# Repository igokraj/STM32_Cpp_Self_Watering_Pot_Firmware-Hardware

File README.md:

# Self Watering Pot

Projekt zakładał stworzenie automatycznej, samopodlewającej się doniczki na mikrokontrolerze STM32F446RE. Firmware jest napisany w C++. System pilnuje wilgotności gleby i sam włącza pompkę, kiedy gleba robi się za sucha. Da się też wymusić podlewanie ręcznie, a system ma kilka zabezpieczeń na wypadek, gdyby coś poszło nie tak (zaklinowana pompa, uszkodzony czujnik, zawieszony program, pusty pojemnik na wodę).

Do obsługi tego systemu spokojnie można by było użyć mikrokontrolera o mniejszej wydajności, liczbie pinów, pamięci..., jednak ze względu na to, że fizycznie do testowania posiadam jedynie NUCLEO-F446RE, to również na płytce PCB użyłem tego mikrokontrolera dla ujednolicenia projektu. Poniżej zamieszczam zdjęcia prototypu na płytce stykowej (jako zamiennik MOSFETa użyłem diody, symulując jego włączanie/wyłączanie, oraz jako czujnika wilgotności używam ręcznego potencjometru, a do czujnika poziomu wody po prostu kabla, który może być wpięty lub wypięty).

This project set out to build an automatic, self-watering plant pot based on the STM32F446RE microcontroller. The firmware is written in C++. The system keeps an eye on soil moisture and turns the pump on by itself once the soil gets too dry. Watering can also be forced manually, and the system has a few safeguards in case something goes wrong (a stuck pump, a broken sensor, a hung program, an empty water container).

This system would honestly run fine on a much smaller microcontroller which would have a less performance, fewer pins, less memory, but since the only board I physically had for testing was a NUCLEO-F446RE, I used the same chip on the PCB too, just to keep the project consistent. Below are photos of the prototype on a breadboard (I used an LED as a stand-in for the MOSFET, to simulate it switching on/off, a regular potentiometer as a stand-in for the moisture sensor, and for the water level sensor just a loose wire that can be plugged in or pulled out).

## Photos

**Breadboard prototype**

**Schematic**

**PCB layout and 3D render**

## How it works

The system has four states: **Waiting**, **Watering**, **EmptyContainer** (no water in the tank), and **Error**.

In the main loop, the program:

1. reads the water level sensor (float switch),
2. handles the Plus/Minus buttons (adjusts the target humidity by 10% per press, with auto-repeat while held) and the manual start button,
3. reads the soil moisture sensor and converts it to a percentage, checking along the way whether the reading looks like a broken/disconnected sensor,
4. decides the state based on that — with priority: pump fault > broken sensor > empty tank > humidity threshold,
5. drives the LEDs, pump, and buzzer, and shows everything on the OLED screen.

Watering kicks in once humidity drops noticeably (by 15 percentage points). If the pump runs continuously for more than 15 seconds, the system treats it as a fault, shuts the pump off for good, and requires a manual reset via the Start button — the buzzer beeps 3 times during this, repeating once a minute.

Holding the Manual Start button forces watering regardless of what the sensor reads.

## Peripherals / electronics

- **STM32F446RETx** — microcontroller
- **Soil moisture sensor** (capacitive) — ADC input
- **Water level sensor** (float switch) — a plain switch
- **3× buttons** — Manual Start, Plus, Minus
- **RGB LED** — indicates system state by color
- **Buzzer** — audible alarm on error
- **Water pump** driven by a MOSFET (IRLZ540N)
- **128×64 OLED display** (SSD1306) over I2C
- **AMS1117-3.3** — 3.3V voltage regulator
- Power connector (barrel jack) with a fuse and overvoltage protection
- SWD connector (ST-Link) for programming/debugging

## BOM (short version)

| Reference      | Component                                                             | Qty |
| --------------- | --------------------------------------------------------------------- | --- |
| U2              | STM32F446RETx                                                         | 1   |
| U1              | AMS1117-3.3 (3.3V regulator)                                          | 1   |
| Q1              | IRLZ540N (MOSFET, pump switch)                                        | 1   |
| RGB1            | RGB LED                                                                | 1   |
| LED1            | LED (status)                                                          | 1   |
| Buzzer1         | Buzzer                                                                 | 1   |
| SW1–SW3         | Buttons (Start/Plus/Minus)                                            | 3   |
| J1              | Power jack (barrel jack)                                               | 1   |
| J5, J6          | Screw terminals (pump, external power)                                | 2   |
| Hum Sensor1     | Moisture sensor connector                                              | 1   |
| OLED1           | OLED display connector                                                 | 1   |
| STLink1         | Programmer connector                                                   | 1   |
| F1              | Fuse                                                                    | 1   |
| D2              | TVS diode (overvoltage protection)                                     | 1   |
| D3, D4, D6–D11  | Schottky diodes                                                        | 8   |
| L1              | Ferrite bead (power filtering)                                         | 1   |
| R, C            | Resistors and capacitors (filtering, pull-up/down, debounce circuits) | ~30 |

The full list (with LCSC part numbers) is in `hardware/Self_Watering_POT/BOM.xlsx` and `All_BOM.xlsx`.

## Firmware

The code is written in **C++** (built on top of the C code generated by STM32CubeMX/HAL). The pot's state logic, debounced button handling, OLED display, and buzzer are written as separate classes/modules — the rest (ADC, timer, GPIO, watchdog) is the generated HAL layer.

## Repo structure

- `firmware/` — CMake project with the STM32 sources
- `hardware/` — KiCad schematic and PCB, production files (Gerbers), BOM
- `Images/` — project photos and renders

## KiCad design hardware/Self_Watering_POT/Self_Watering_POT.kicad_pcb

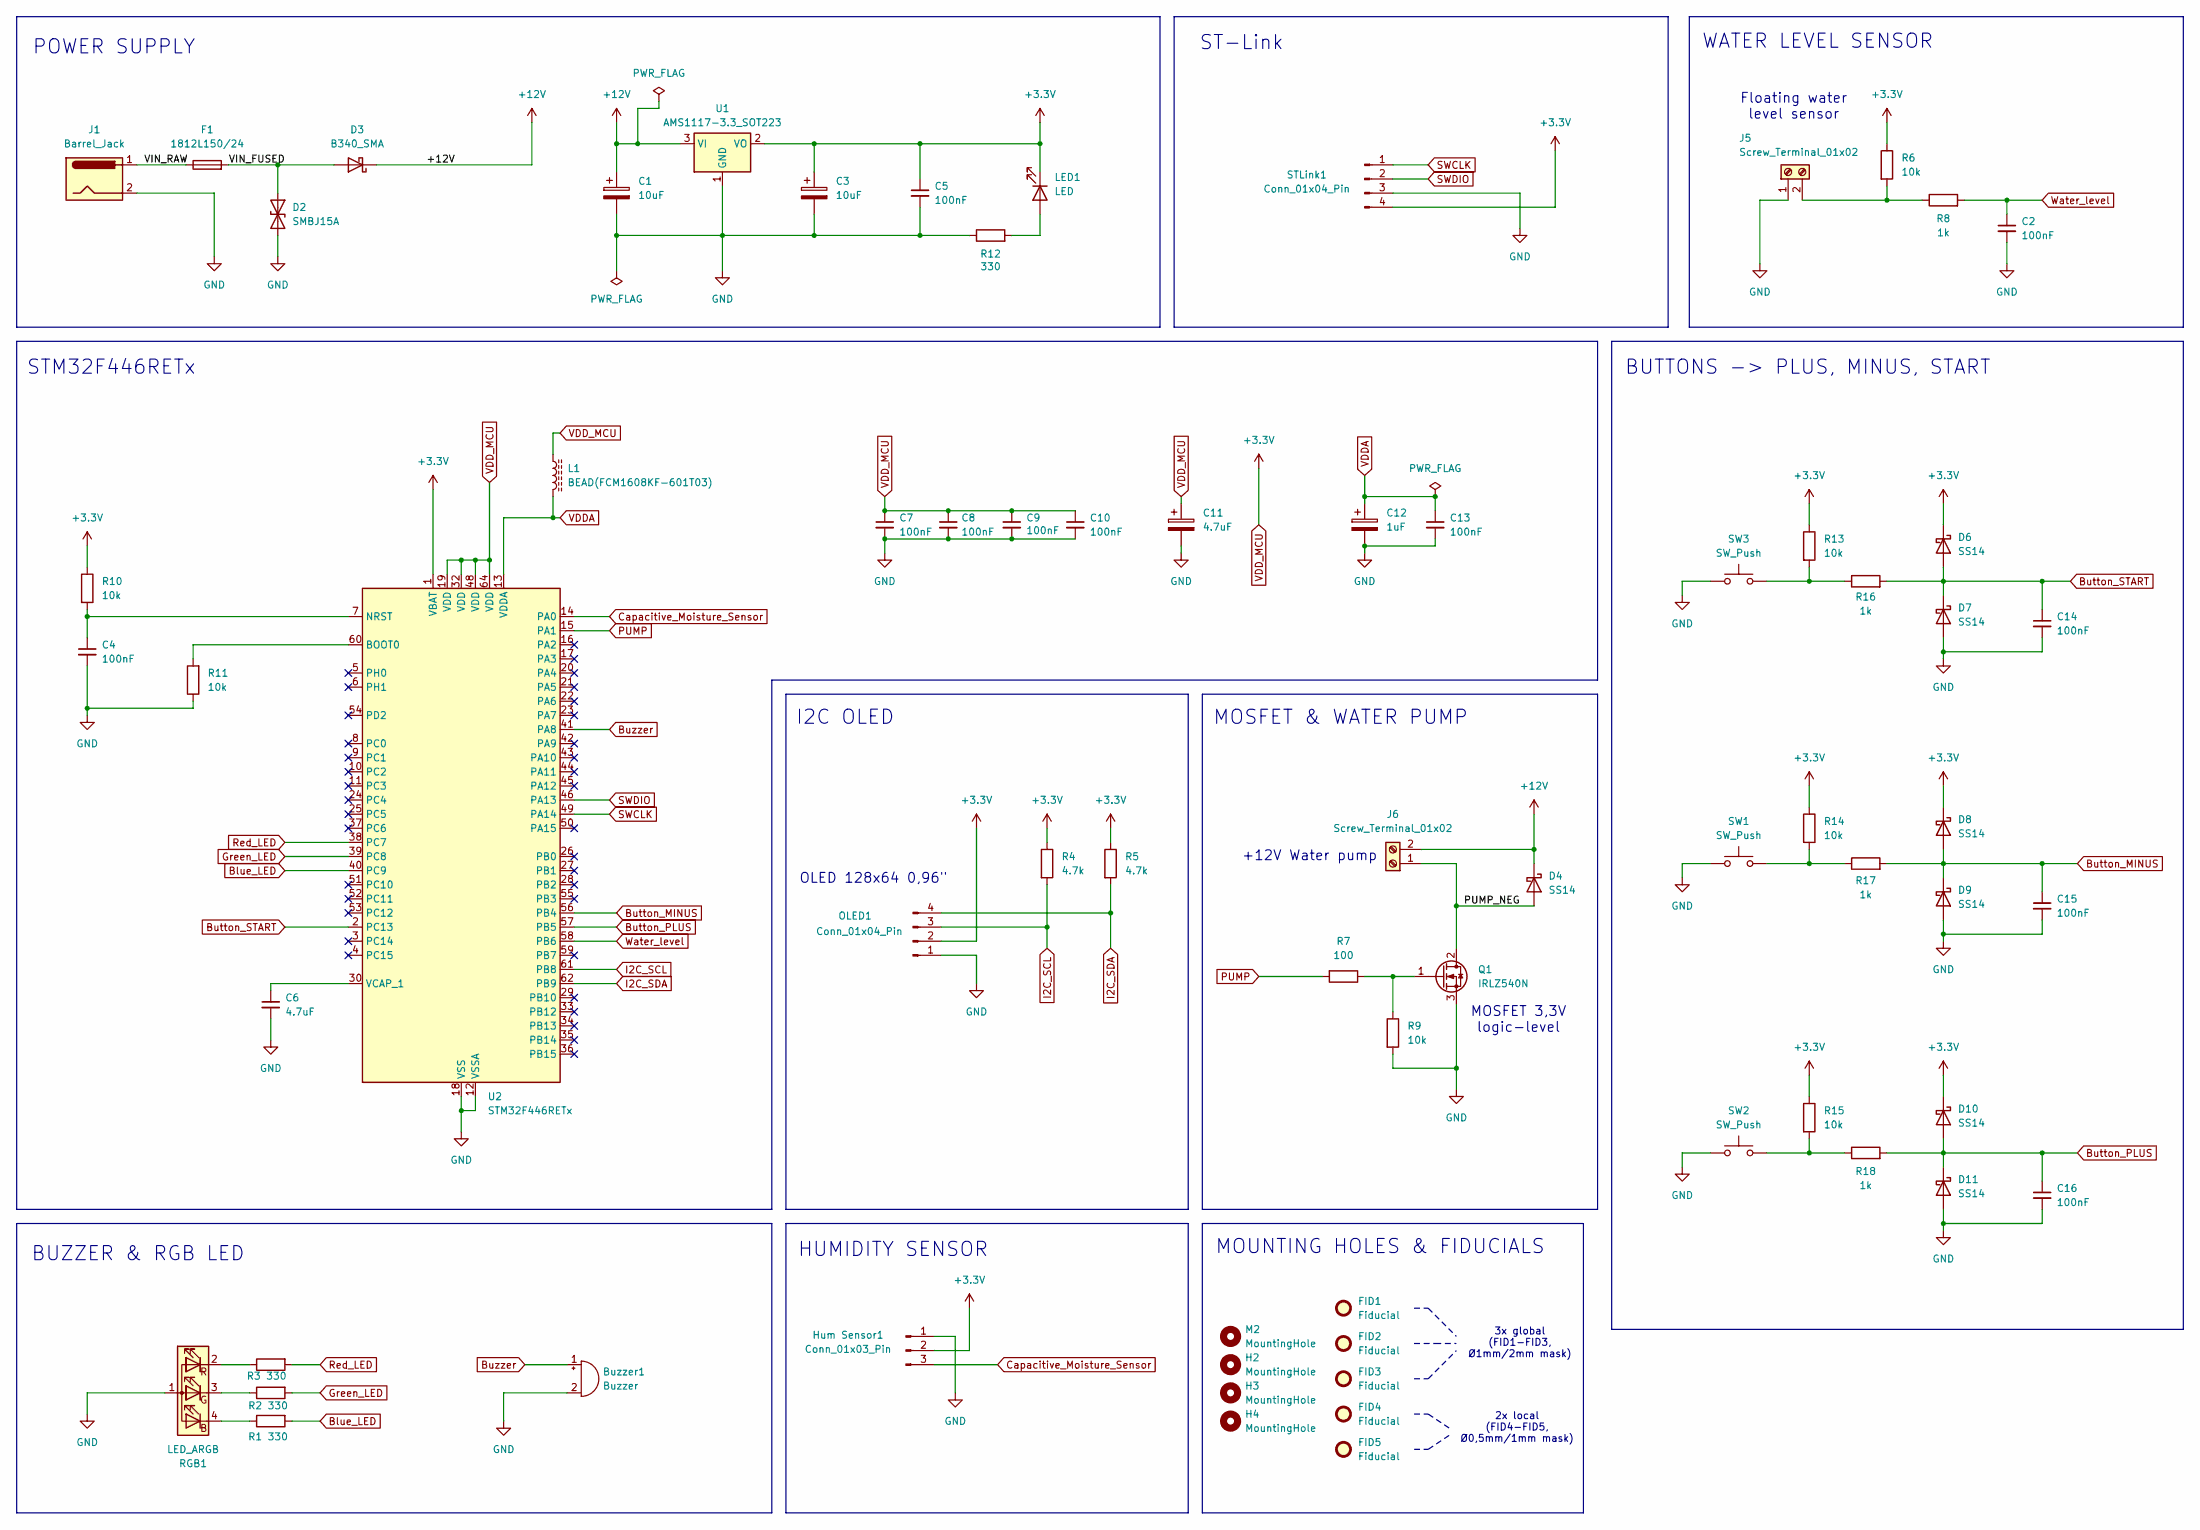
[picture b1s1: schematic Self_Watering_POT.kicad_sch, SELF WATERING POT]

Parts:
Buzzer1: Buzzer; Buzzer_12x9.5RM7.6
C1, C3: 10uF; CP_EIA-3216-18_Kemet-A
C2, C4, C5, C7, C8, C9, C10, C13, C14, C15, C16: 100nF; C_0805_2012Metric
C6, C11: 4.7uF; CP_EIA-3216-18_Kemet-A
C12: 1uF; C_1210_3225Metric
D2: SMBJ15A; D_SMB
D3: B340_SMA; D_SMA
D4, D6, D7, D8, D9, D10, D11: SS14; D_SMA
F1: 1812L150/24; Fuse_1812_4532Metric
FID1, FID2, FID3: Fiducial; Fiducial_1mm_Mask2mm
FID4, FID5: Fiducial; Fiducial_0.5mm_Mask1mm
H2, H3, H4: MountingHole; MountingHole_2.2mm_M2
Hum Sensor1: Conn_01x03_Pin; PinHeader_1x03_P2.54mm_Vertical
J1: Barrel_Jack; BarrelJack_Horizontal
J5, J6: Screw_Terminal_01x02; TerminalBlock_Phoenix_MKDS-1,5-2-5.08_1x02_P5.08mm_Horizont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
L1: BEAD(FCM1608KF-601T03); L_0603_1608Metric
LED1: LED; LED_D5.0mm
M2: MountingHole; MountingHole_2.2mm_M2
OLED1: Conn_01x04_Pin; PinSocket_1x04_P2.54mm_Vertical
Q1: IRLZ540N; TO-220-3_Vertical
R1, R2, R3, R12: 330; R_0805_2012Metric
R4, R5: 4.7k; R_0805_2012Metric
R6, R9, R10, R11, R13, R14, R15: 10k; R_0805_2012Metric
R7: 100; R_0805_2012Metric
R8, R16, R17, R18: 1k; R_0805_2012Metric
RGB1: LED_ARGB; LED_D5.0mm-4_RGB
STLink1: Conn_01x04_Pin; PinHeader_1x04_P2.54mm_Vertical
SW1, SW2, SW3: SW_Push; SW_PUSH_6mm
U1: AMS1117-3.3_SOT223; SOT-223-3_TabPin2
U2: STM32F446RETx; LQFP-64_10x10mm_P0.5mm

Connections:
+12V: C1.1, D3.1 (K), D4.1 (K), J6.2, U1.3 (VI)
/PUMP_NEG: D4.2 (A), J6.1, Q1.2 (D)
/VIN_FUSED: D2.1 (A1), D3.2 (A), F1.2
/VIN_RAW: F1.1, J1.1
Blue_LED: R1.2, U2.40 (PC9)
Button_MINUS: C15.1, D8.2 (A), D9.1 (K), R17.2, U2.56 (PB4)
Button_PLUS: C16.1, D10.2 (A), D11.1 (K), R18.2, U2.57 (PB5)
Button_START: C14.1, D6.2 (A), D7.1 (K), R16.2, U2.2 (PC13)
Buzzer: Buzzer1.1 (+), U2.41 (PA8)
Capacitive_Moisture_Sensor: Hum Sensor1.3, U2.14 (PA0)
GND: Buzzer1.2 (-), C1.2, C2.2, C3.2, C4.2, C5.2, C6.2, C7.2, C8.2, C9.2, C10.2, C11.2, C12.2, C13.2, C14.2, C15.2, C16.2, D2.2 (A2), D7.2 (A), D9.2 (A), D11.2 (A), Hum Sensor1.1, J1.2, J5.1, OLED1.1, Q1.3 (S), R9.2, R11.1, R12.1, RGB1.1 (A), STLink1.3, SW1.1, SW2.1, SW3.1, U1.1 (GND), U2.12 (VSSA), U2.18 (VSS), U2.31 (VSS), U2.47 (VSS), U2.63 (VSS)
Green_LED: R2.2, U2.39 (PC8)
I2C_SCL: OLED1.3, R4.2, U2.61 (PB8)
I2C_SDA: OLED1.4, R5.2, U2.62 (PB9)
unnamed: J5.2, R6.2, R8.1
unnamed: LED1.2 (A), R12.2
unnamed: Q1.1 (G), R7.1, R9.1
unnamed: R13.2, R16.1, SW3.2
unnamed: R14.2, R17.1, SW1.2
unnamed: R15.2, R18.1, SW2.2
unnamed: R1.1, RGB1.4 (BK)
unnamed: R2.1, RGB1.3 (GK)
unnamed: R3.1, RGB1.2 (RK)
unnamed: R11.2, U2.60 (BOOT0)
unnamed: C4.1, R10.2, U2.7 (NRST)
unnamed: C6.1, U2.30 (VCAP_1)
PUMP: R7.2, U2.15 (PA1)
Red_LED: R3.2, U2.38 (PC7)
SWCLK: STLink1.1, U2.49 (PA14)
SWDIO: STLink1.2, U2.46 (PA13)
VDDA: C12.1, C13.1, L1.2, U2.13 (VDDA)
VDD_MCU: C3.1, C5.1, C7.1, C8.1, C9.1, C10.1, C11.1, D6.1 (K), D8.1 (K), D10.1 (K), Hum Sensor1.2, L1.1, LED1.1 (K), OLED1.2, R4.1, R5.1, R6.1, R10.1, R13.1, R14.1, R15.1, STLink1.4, U1.2 (VO), U2.1 (VBAT), U2.19 (VDD), U2.32 (VDD), U2.48 (VDD), U2.64 (VDD)
Water_level: C2.1, R8.2, U2.58 (PB6)

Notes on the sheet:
+12V Water pump
2x local (FID4-FID5, Ø0,5mm/1mm mask)
MOSFET 3,3V logic-level
OLED 128x64 0,96"
BUZZER & RGB LED
BUTTONS -> PLUS, MINUS, START
I2C OLED
MOUNTING HOLES & FIDUCIALS
Floating water level sensor
POWER SUPPLY
STM32F446RETx
MOSFET & WATER PUMP
HUMIDITY SENSOR
WATER LEVEL SENSOR
ST-Link
3x global (FID1-FID3, Ø1mm/2mm mask)

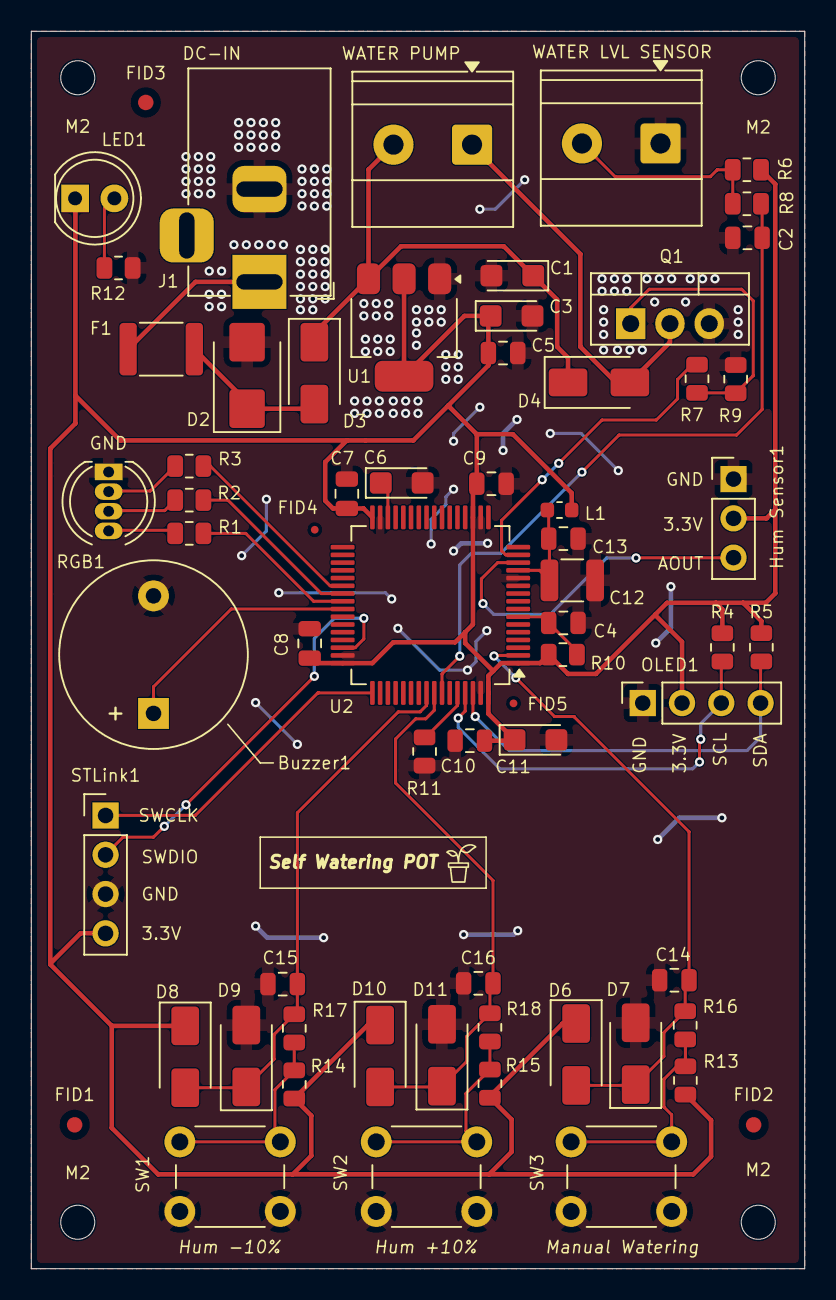
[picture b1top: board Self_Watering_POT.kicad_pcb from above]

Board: 2 copper layers, 50.0 x 80.0 mm, 69 parts (0 on the bottom side), 33 nets.

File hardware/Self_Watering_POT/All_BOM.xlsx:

Reference | Qty | Value | DNP | Exclude from BOM | Exclude from Board | Footprint | Datasheet
Buzzer1 | 1 | Buzzer |  |  |  | Buzzer_Beeper:Buzzer_12x9.5RM7.6
C1,C3 | 2 | 10uF |  |  |  | Capacitor_Tantalum_SMD:CP_EIA-3216-18_Kemet-A
C2,C4,C5,C7,C8,C9,C10,C13,C14,C15,C16 | 11 | 100nF |  |  |  | Capacitor_SMD:C_0805_2012Metric
C6,C11 | 2 | 4.7uF |  |  |  | Capacitor_Tantalum_SMD:CP_EIA-3216-18_Kemet-A
C12 | 1 | 1uF |  |  |  | Capacitor_SMD:C_1210_3225Metric
D2 | 1 | SMBJ15A |  |  |  | Diode_SMD:D_SMB
D3 | 1 | B340_SMA |  |  |  | Diode_SMD:D_SMA
D4,D6,D7,D8,D9,D10,D11 | 7 | SS14 |  |  |  | Diode_SMD:D_SMA
F1 | 1 | 1812L150/24 |  |  |  | Fuse:Fuse_1812_4532Metric
Hum Sensor1 | 1 | Conn_01x03_Pin |  |  |  | Connector_PinHeader_2.54mm:PinHeader_1x03_P2.54mm_Vertical
J1 | 1 | Barrel_Jack |  |  |  | Connector_BarrelJack:BarrelJack_Horizontal
J5,J6 | 2 | Screw_Terminal_01x02 |  |  |  | TerminalBlock_Phoenix:TerminalBlock_Phoenix_MKDS-1,5-2-5.08_1x02_P5.08mm_Horizo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
L1 | 1 | BEAD(FCM1608KF-601T03) |  |  |  | Inductor_SMD:L_0603_1608Metric
LED1 | 1 | LED |  |  |  | LED_THT:LED_D5.0mm
OLED1 | 1 | Conn_01x04_Pin |  |  |  | Connector_PinSocket_2.54mm:PinSocket_1x04_P2.54mm_Vertical
Q1 | 1 | IRLZ540N |  |  |  | Package_TO_SOT_THT:TO-220-3_Vertical
R1,R2,R3,R12 | 4 | 330 |  |  |  | Resistor_SMD:R_0805_2012Metric
R4,R5 | 2 | 4.7k |  |  |  | Resistor_SMD:R_0805_2012Metric
R6,R9,R10,R11,R13,R14,R15 | 7 | 10k |  |  |  | Resistor_SMD:R_0805_2012Metric
R7 | 1 | 100 |  |  |  | Resistor_SMD:R_0805_2012Metric
R8,R16,R17,R18 | 4 | 1k |  |  |  | Resistor_SMD:R_0805_2012Metric
RGB1 | 1 | LED_ARGB |  |  |  | LED_THT:LED_D5.0mm-4_RGB
STLink1 | 1 | Conn_01x04_Pin |  |  |  | Connector_PinHeader_2.54mm:PinHeader_1x04_P2.54mm_Vertical
SW1,SW2,SW3 | 3 | SW_Push |  |  |  | Button_Switch_THT:SW_PUSH_6mm
U1 | 1 | AMS1117-3.3_SOT223 |  |  |  | Package_TO_SOT_SMD:SOT-223-3_TabPin2 | http://www.advanced-monolithic.com/pdf/ds1117.pdf
U2 | 1 | STM32F446RETx |  |  |  | Package_QFP:LQFP-64_10x10mm_P0.5mm | https://www.st.com/resource/en/datasheet/stm32f446re.pdf

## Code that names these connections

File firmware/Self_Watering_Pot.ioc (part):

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Mcu.Name=STM32F446R(C-E)Tx
Mcu.Package=LQFP64
Mcu.UserName=STM32F446RETx
PA0-WKUP.GPIOParameters=GPIO_Label
PA0-WKUP.GPIO_Label=ADC1_Hum
PA0-WKUP.Signal=ADCx_IN0
PA1.GPIOParameters=GPIO_Label
PA1.GPIO_Label=Pump_on
PA1.Signal=GPIO_Output
PA13.GPIOParameters=GPIO_Label
PA13.GPIO_Label=TMS
PA13.Mode=Serial_Wire
PA13.Signal=SYS_JTMS-SWDIO
PA14.GPIOParameters=GPIO_Label
PA14.GPIO_Label=TCK
PA14.Mode=Serial_Wire
PA14.Signal=SYS_JTCK-SWCLK
PA2.GPIOParameters=GPIO_Label
PA2.GPIO_Label=USART_TX
PA2.Mode=Asynchronous
PA2.Signal=USART2_TX
PA3.GPIOParameters=GPIO_Label
PA3.GPIO_Label=USART_RX
PA3.Mode=Asynchronous
PA3.Signal=USART2_RX
PA8.GPIOParameters=GPIO_Label
PA8.GPIO_Label=Buzzer_Status
PA8.Signal=GPIO_Output
PB3.GPIOParameters=GPIO_Label
PB3.GPIO_Label=SWO
PB3.Signal=SYS_JTDO-SWO
PB4.GPIOParameters=GPIO_PuPd,GPIO_Label
PB4.GPIO_Label=Button_Minus
PB4.GPIO_PuPd=GPIO_PULLUP
PB4.Signal=GPIO_Input
PB5.GPIOParameters=GPIO_PuPd,GPIO_Label
PB5.GPIO_Label=Button_Plus
PB5.GPIO_PuPd=GPIO_PULLUP
PB5.Signal=GPIO_Input
PB6.GPIOParameters=GPIO_PuPd,GPIO_Label
PB6.GPIO_Label=Water_level
PB6.GPIO_PuPd=GPIO_PULLUP
PB6.Signal=GPIO_Input
PB8.Mode=I2C
PB8.Signal=I2C1_SCL
PB9.Mode=I2C
PB9.Signal=I2C1_SDA
PC13.GPIOParameters=GPIO_PuPd,GPIO_Label,GPIO_ModeDefaultEXTI
PC13.GPIO_Label=Start_Button
PC13.GPIO_ModeDefaultEXTI=GPIO_MODE_IT_RISING_FALLING
PC13.GPIO_PuPd=GPIO_PULLUP
PC13.Signal=GPXTI13
PC14-OSC32_IN.Mode=LSE-External-Oscillator
PC14-OSC32_IN.Signal=RCC_OSC32_IN
PC15-OSC32_OUT.Mode=LSE-External-Oscillator
PC15-OSC32_OUT.Signal=RCC_OSC32_OUT
PC7.GPIOParameters=GPIO_Label
PC7.GPIO_Label=Red_LED
PC7.Signal=GPIO_Output
PC8.GPIOParameters=GPIO_Label
PC8.GPIO_Label=Green_LED
PC8.Signal=GPIO_Output
PC9.GPIOParameters=GPIO_Label
PC9.GPIO_Label=Blue_LED
PC9.Signal=GPIO_Output
PH0-OSC_IN.Mode=HSE-External-Oscillator
PH0-OSC_IN.Signal=RCC_OSC_IN
PH1-OSC_OUT.Mode=HSE-External-Oscillator
PH1-OSC_OUT.Signal=RCC_OSC_OUT
RCC.HSE_VALUE=8000000
RCC.SYSCLKFreq_VALUE=84000000
RCC.SYSCLKSource=RCC_SYSCLKSOURCE_PLLCLK
board=NUCLEO-F446RE
boardIOC=true
